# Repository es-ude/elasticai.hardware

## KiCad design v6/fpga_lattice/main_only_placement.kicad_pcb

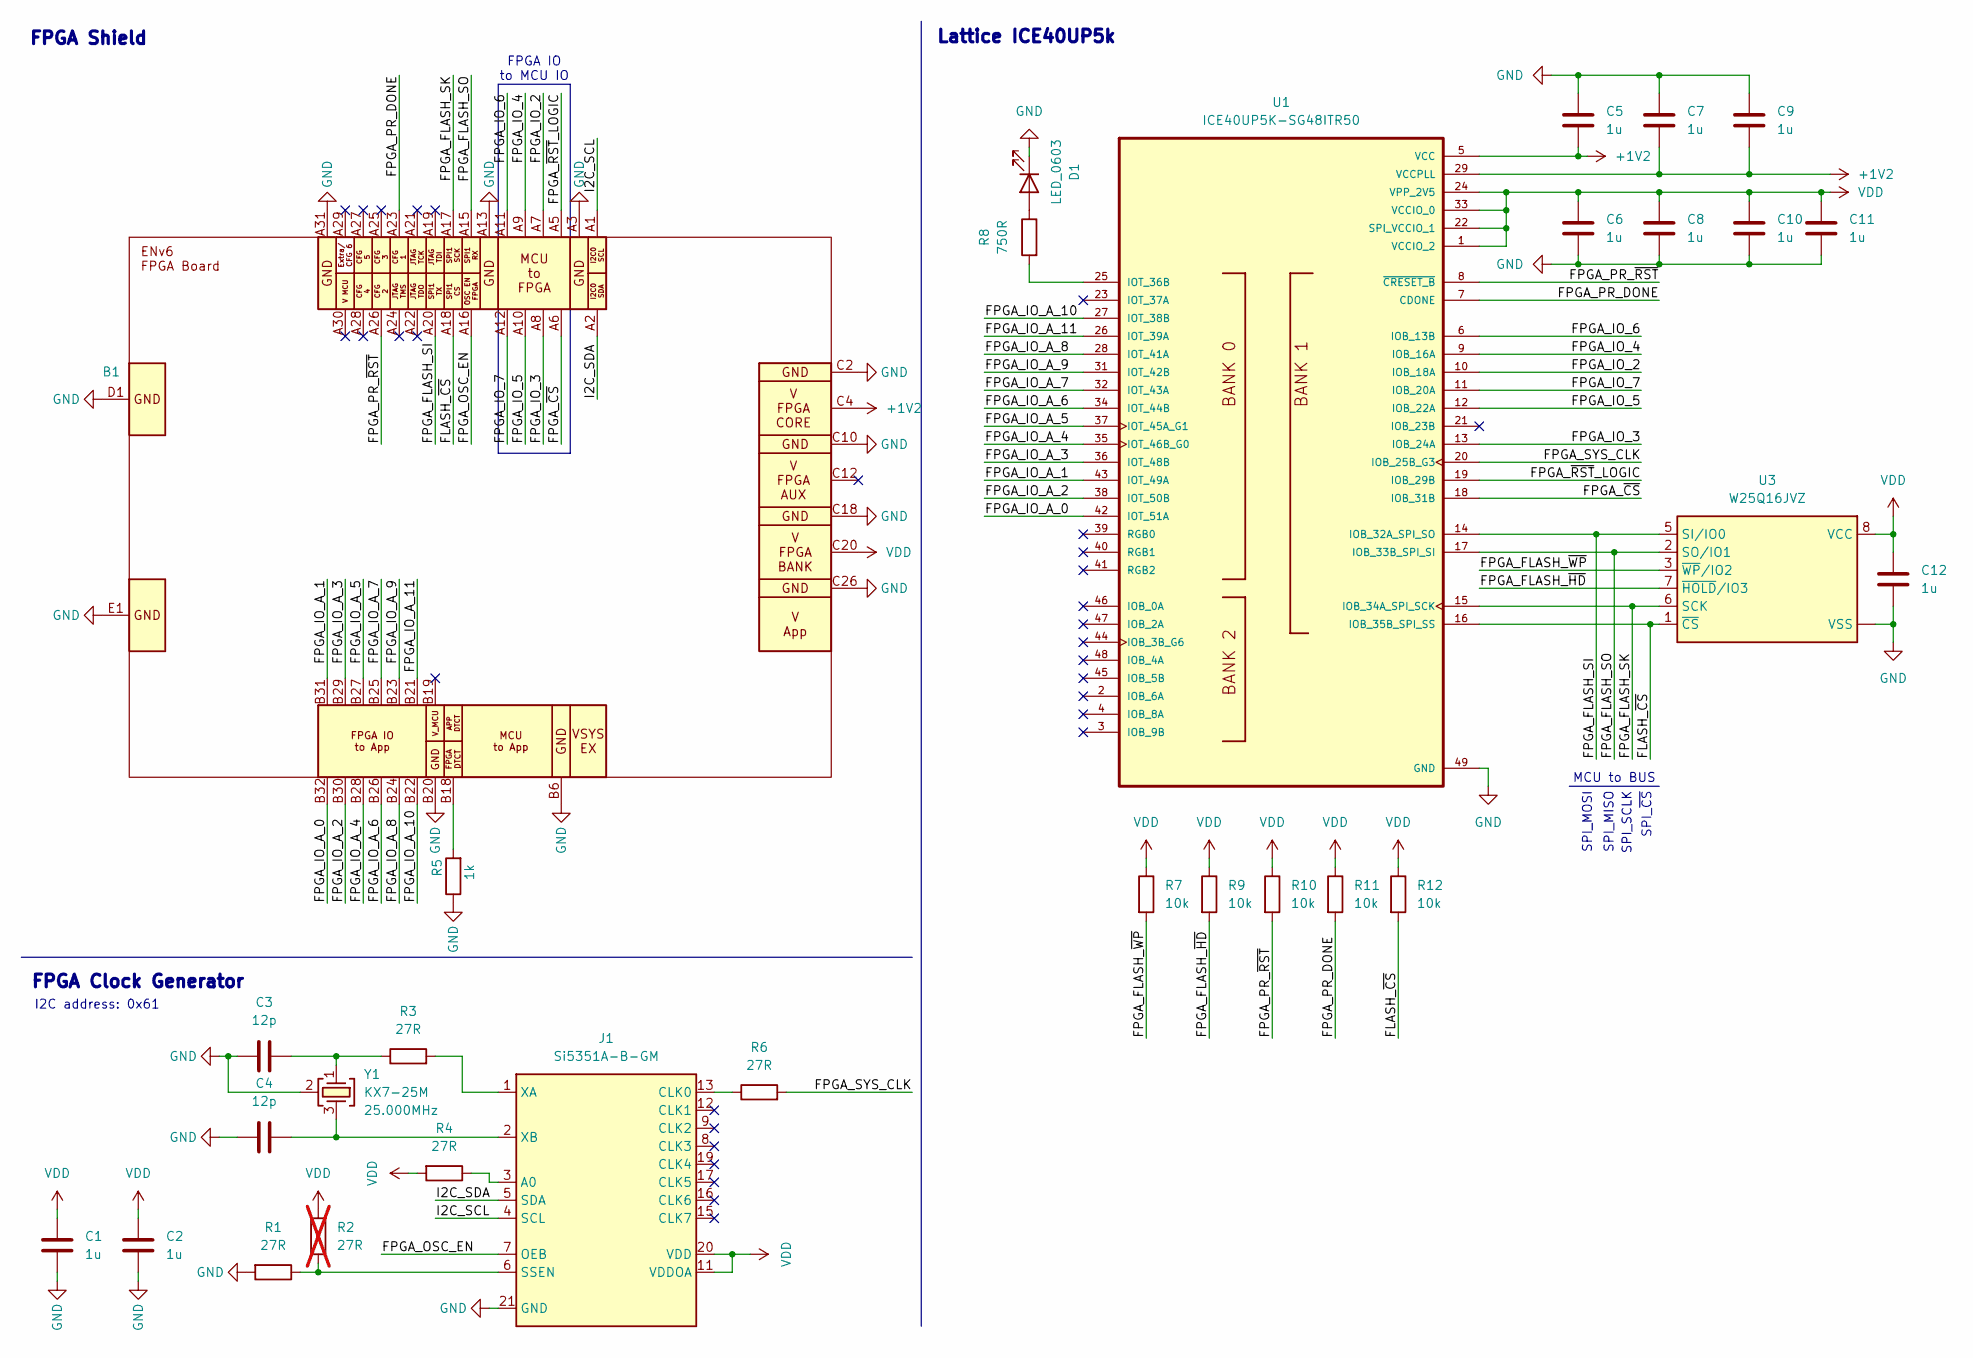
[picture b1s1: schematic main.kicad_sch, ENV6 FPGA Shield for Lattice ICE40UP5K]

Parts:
B1: ExtensionBoard_ENv6
C1, C2, C5, C6, C7, C8, C9, C10, C11, C12: 1u; C_0402_1005Metric
C3, C4: 12p; C_0402_1005Metric
D1: LED_0603; LED_0603_1608Metric
J1: Si5351A-B-GM; QFN-20-1EP_4x4mm_P0.5mm_EP2.7x2.7mm
R1, R3, R4, R6: 27R; R_0402_1005Metric
R2: 27R; R_0402_1005Metric; not fitted
R5: 1k; R_0402_1005Metric
R7, R9, R10, R11, R12: 10k; R_0402_1005Metric
R8: 750R; R_0402_1005Metric
U1: ICE40UP5K-SG48ITR50; QFN-48-1EP_7x7mm_P0.5mm_EP5.15x5.15mm; PARTREV 1.4
U3: W25Q16JVZ; WSON-8-1EP_6x5mm_P1.27mm_EP3.4x4.3mm
Y1: KX7-25M; KX-7; MPN 12.60417

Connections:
+1V2: B1.C3, B1.C4, B1.C5, B1.C6, B1.C7, B1.C8, C5.2, C7.2, C9.2, U1.5 (VCC), U1.29 (VCCPLL), U1.30 (VCC)
/FLASH_~CS: B1.A18, R12.2, U1.16 (IOB_35B_SPI_SS), U3.1 (~CS); also elsewhere on the board
/FPGA_FLASH_SI: B1.A20, U1.14 (IOB_32A_SPI_SO), U3.5 (SI/IO0); also elsewhere on the board
/FPGA_FLASH_SK: B1.A17, U1.15 (IOB_34A_SPI_SCK), U3.6 (SCK); also elsewhere on the board
/FPGA_FLASH_SO: B1.A15, U1.17 (IOB_33B_SPI_SI), U3.2 (SO/IO1); also elsewhere on the board
/FPGA_FLASH_~HD: R9.2, U3.7 (~HOLD/IO3); also elsewhere on the board
/FPGA_FLASH_~WP: R7.2, U3.3 (~WP/IO2); also elsewhere on the board
/FPGA_IO_2: B1.A7, U1.10 (IOB_18A)
/FPGA_IO_3: B1.A8, U1.13 (IOB_24A)
/FPGA_IO_4: B1.A9, U1.9 (IOB_16A)
/FPGA_IO_5: B1.A10, U1.12 (IOB_22A)
/FPGA_IO_6: B1.A11, U1.6 (IOB_13B)
/FPGA_IO_7: B1.A12, U1.11 (IOB_20A)
/FPGA_IO_A_0: B1.B32, U1.42 (IOT_51A)
/FPGA_IO_A_1: B1.B31, U1.43 (IOT_49A)
/FPGA_IO_A_2: B1.B30, U1.38 (IOT_50B)
/FPGA_IO_A_3: B1.B29, U1.36 (IOT_48B)
/FPGA_IO_A_4: B1.B28, U1.35 (IOT_46B_G0)
/FPGA_IO_A_5: B1.B27, U1.37 (IOT_45A_G1)
/FPGA_IO_A_6: B1.B26, U1.34 (IOT_44B)
/FPGA_IO_A_7: B1.B25, U1.32 (IOT_43A)
/FPGA_IO_A_8: B1.B24, U1.28 (IOT_41A)
/FPGA_IO_A_9: B1.B23, U1.31 (IOT_42B)
/FPGA_IO_A_10: B1.B22, U1.27 (IOT_38B)
/FPGA_IO_A_11: B1.B21, U1.26 (IOT_39A)
/FPGA_OSC_EN: B1.A16, J1.7 (OEB)
/FPGA_PR_DONE: B1.A23, R11.2, U1.7 (CDONE)
/FPGA_PR_~RST: B1.A26, R10.2, U1.8 (~CRESET_B)
/FPGA_SYS_CLK: R6.2, U1.20 (IOB_25B_G3)
/FPGA_~CS: B1.A6, U1.18 (IOB_31B)
/FPGA_~RST_LOGIC: B1.A5, U1.19 (IOB_29B)
/I2C_SCL: B1.A1, J1.4 (SCL)
/I2C_SDA: B1.A2, J1.5 (SDA)
GND: B1.A3, B1.A4, B1.A13, B1.A14, B1.A31, B1.A32, B1.B5, B1.B6, B1.B20, B1.C1, B1.C2, B1.C9, B1.C10, B1.C17, B1.C18, B1.C25, B1.C26, B1.D1, B1.D2, B1.D3, B1.D4, B1.D5, B1.D6, B1.D7, B1.D8, B1.E1, B1.E2, B1.E3, B1.E4, B1.E5, B1.E6, B1.E7, B1.E8, C1.2, C2.2, C3.2, C4.2, C5.1, C6.2, C7.1, C8.2, C9.1, C10.2, C11.2, C12.2, D1.1 (K), J1.21 (GND), R1.2, R5.1, U1.49 (GND), U3.4 (VSS), U3.9 (VSS), Y1.2 (SH), Y1.4 (SH); also elsewhere on the board
unnamed: B1.B18, R5.2
unnamed: C3.1, R3.1, Y1.1
unnamed: D1.2 (A), R8.1
unnamed: J1.3 (A0), R4.1
unnamed: J1.13 (CLK0), R6.1
unnamed: J1.6 (SSEN), R1.1, R2.1
unnamed: J1.1 (XA), R3.2
unnamed: C4.1, J1.2 (XB), Y1.3
unnamed: R8.2, U1.25 (IOT_36B)
VDD: B1.C19, B1.C20, B1.C21, B1.C22, B1.C23, B1.C24, C1.1, C2.1, C6.1, C8.1, C10.1, C11.1, C12.1, J1.10 (VDDOB), J1.11 (VDDOA), J1.14 (VDDOD), J1.18 (VDDOC), J1.20 (VDD), R2.2, R4.2, R7.1, R9.1, R10.1, R11.1, R12.1, U1.1 (VCCIO_2), U1.22 (SPI_VCCIO_1), U1.24 (VPP_2V5), U1.33 (VCCIO_0), U3.8 (VCC); also elsewhere on the board

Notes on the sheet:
SPI_MOSI
FPGA IO to MCU IO
SPI_SCLK
MCU to BUS
SPI_MISO
I2C address: 0x61
SPI_~{CS}
FPGA Clock Generator
FPGA Shield
Lattice ICE40UP5k

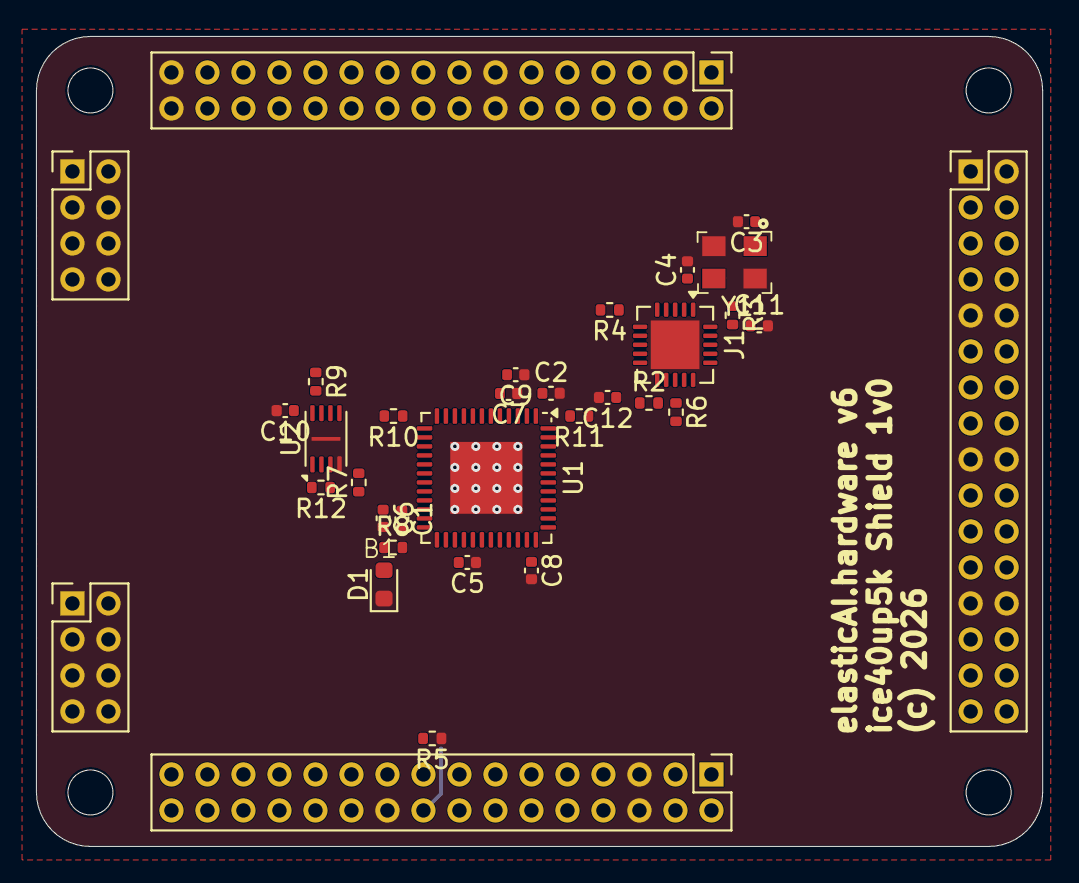
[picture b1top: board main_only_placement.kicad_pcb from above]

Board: 2 copper layers, 55.9 x 45.0 mm, 30 parts (1 on the bottom side), 44 nets.

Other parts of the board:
U2: W25Q16JVUX; USON-8-1EP_3x2mm_P0.5mm_EP0.2x1.6mm

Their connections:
/FLASH_~CS: U2.1 (~CS); also elsewhere on the board
/FPGA_FLASH_SI: U2.5 (SI/IO0); also elsewhere on the board
/FPGA_FLASH_SK: U2.6 (SCK); also elsewhere on the board
/FPGA_FLASH_SO: U2.2 (SO/IO1); also elsewhere on the board
/FPGA_FLASH_~HD: U2.7 (~HOLD/IO3); also elsewhere on the board
/FPGA_FLASH_~WP: U2.3 (~WP/IO2); also elsewhere on the board
GND: U2.4 (VSS), U2.9 (VSS); also elsewhere on the board
VDD: U2.8 (VCC); also elsewhere on the board

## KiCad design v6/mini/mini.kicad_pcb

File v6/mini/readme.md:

# ENv6.mini

Single-board version of the ENv6 platform (revision 1v1): an MCU, an iCE40UP5K FPGA, a power monitor and a PMOD connector on one PCB. It is the smallest entry point / minimal version to the ENv6 idea (MCU-controlled FPGA configuration and per-rail current measurement).
For further details, please look into the [iBOM v1.1](bom/ibom_1v1.html).

## State
Active. Please use the following firmware from this [repo](https://github.com/es-ude/elasticai_runtime_env6mini).

## Concept
ENv6.mini integrates the essentials of the stack on one PCB:
- **MCU:** an RP2350A (U8) with its own QSPI flash (U7), 12 MHz crystal (Y1), USB-C (J1) for power and data, an SWD connector (J3), BOOT/RST buttons (S1, S2) and a WS2812B status LED (D2). The MCU is the master of the board: it configures the FPGA, controls its power and talks to it over SPI.
- **FPGA:** a Lattice iCE40UP5K (U5) with a bitstream flash (U6, W25Q16). The MCU writes the bitstream to this flash over a dedicated flash SPI (SK, SI, SO, CS) and controls the FPGA with `FPGA_RST` (active low); `FPGA_DONE` reports a finished configuration. The control lines `FPGA_CLK`, `FPGA_RST_LOGIC` (active low) and `FPGA_GPIO0 … 5` as well as a second I2C (`I2C_FPGA_SCL/SDA`) connect MCU and FPGA at runtime.
- **User logic:** the FPGA runs the accelerator; data is exchanged with the MCU over the SPI bus (SCLK, MOSI, MISO, CS). Eight FPGA pins (`PMOD_D0 … 7`) are routed to a PMOD connector (U4) at the I/O voltage `VCCQ` for sensors and peripherals.
- **Power and measurement:** two LDOs generate 1.2 V (U2, FPGA core) and 3.3 V (U9, MCU and FPGA I/O). Their outputs pass a PAC1954 power monitor (U1, 1 Ω shunts, I2C, enable `EN_PAC`), so the MCU can measure current and power of the FPGA rails. The FPGA supply can be switched with `PWR_EN_FPGA`. The FPGA I/O bank and the PMOD run at `VCCQ`.

### Differences to the ENv6 stack

|                      | ENv6.mini                  | ENv6 stack                                                |
|----------------------|----------------------------|-----------------------------------------------------------|
| MCU                  | RP2350A                    | RP2354B                                                   |
| FPGA                 | iCE40UP5K, fixed           | exchangeable FPGA board                                   |
| Power                | USB-C, two fixed LDOs      | USB-C / Li-ion, programmable LP873300 with four rails     |
| Current measurement  | PAC1954 on the LDO outputs | PAC1954 on the four programmable rails (or external PPK2) |
| Extension            | PMOD (8 FPGA I/Os)         | MCU/FPGA, application and power headers                   |
| Board identification | –                          | ID resistors, read by the MCU                             |
| Radio / storage      | –                          | Raspberry Pi radio module, microSD                        |

## Contents

| Block (KiCad sheet)                        | Main parts                                                                                                                              |
|--------------------------------------------|-----------------------------------------------------------------------------------------------------------------------------------------|
| MCU (`mcu.kicad_sch`)                      | RP2350A (U8), 12 MHz crystal (Y1), W25Q16 QSPI flash (U7), SWD connector (J3), WS2812B (D2), BOOT / RST buttons (S1, S2), SMA connector |
| FPGA (`fpga.kicad_sch`)                    | Lattice iCE40UP5K-SG48 (U5), W25Q16 bitstream flash (U6), PMOD with 8 GPIOs at VCCQ (U4), status LED, SMA connector                     |
| Connectors / power (`connector.kicad_sch`) | USB-C (J1), PAC1954 (U1, 1 Ω shunts), LDO 1.2 V TLV73312 (U2), LDO 3.3 V TLV73333 (U9)                                                  |

## Interfaces MCU ↔ FPGA

| Interface              | Signals                                                                                |
|------------------------|----------------------------------------------------------------------------------------|
| SPI bus (user logic)   | SCLK, MOSI, MISO, CS                                                                   |
| Flash SPI (bitstream)  | SK, SI, SO, CS                                                                         |
| Control                | `FPGA_CLK`, `FPGA_RST`, `FPGA_RST_LOGIC`, `FPGA_DONE`, `FPGA_GPIO0 … 5`, `PWR_EN_FPGA` |
| I2C to the FPGA        | `I2C_FPGA_SCL`, `I2C_FPGA_SDA`                                                         |
| I2C to the PAC1954     | `I2C_SDA`, `I2C_SCL`, `EN_PAC`                                                         |

Supply rails: VBUS → LDO 1.2 V (FPGA core), LDO 3.3 V (MCU, FPGA I/O), `VCCQ` (FPGA bank, PMOD).

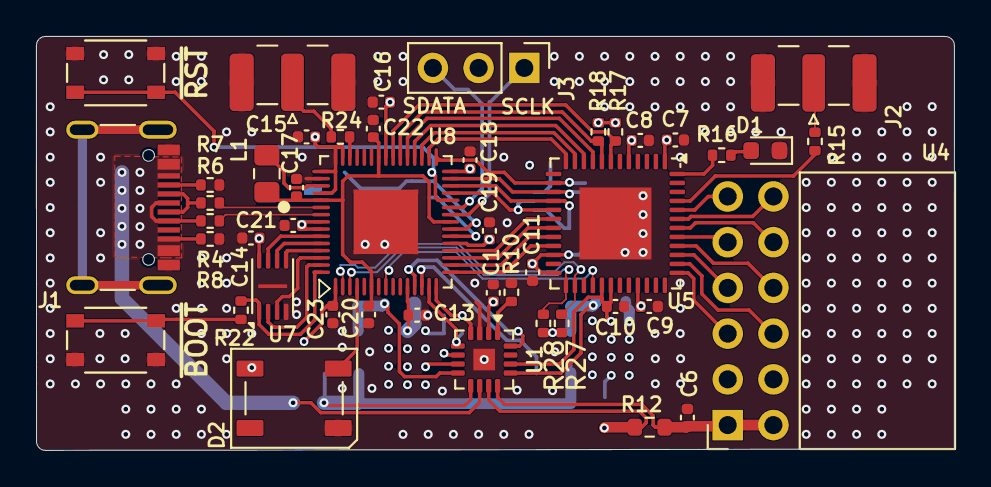
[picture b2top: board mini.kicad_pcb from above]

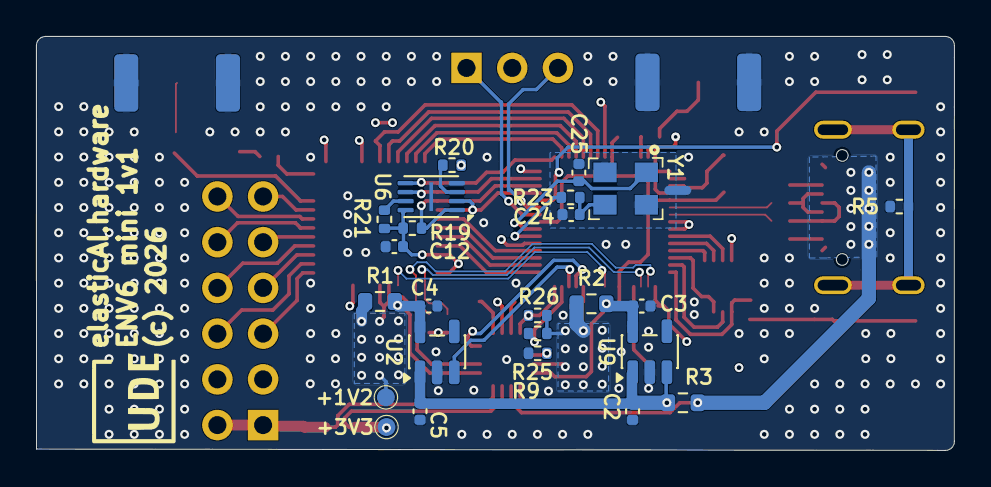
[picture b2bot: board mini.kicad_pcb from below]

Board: 4 copper layers, 51.0 x 23.0 mm, 71 parts (25 on the bottom side), 71 nets.

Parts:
C1, C2, C3, C4, C5, C6, C7, C8, C9, C10, C11, C12, C13, C14, C15, C16, C17, C18, C19, C20, C21, C22, C23: 10u; C_0402_1005Metric
C24, C25: 16p; C_0402_1005Metric
D1: LED_0603; LED_0603_1608Metric
D2: WS2812B; LED_WS2812B_PLCC4_5.0x5.0mm_P3.2mm
J1: USB-C Receptable (16P); USB_C_Receptacle_16P
J2, J4: SMA-FEMALE-H; SMA_Samtec_SMA-J-P-H-ST-EM1_EdgeMount
J3: Pico Debugger (SWD); PinHeader_1x03_P2.54mm_Vertical
L1: 3µ3; L_0805_2012_metric_Alligned_HandSolder
NT1: NetTie_2; NetTie-2_SMD_Pad0.5mm
R1, R2, R3, R12: 1R; R_0603_1608Metric
R4, R6: 27R4; R_0402_1005Metric
R5, R7, R8, R17, R18, R19, R20, R21, R22, R25, R26, R27, R28: 5k1; R_0402_1005Metric
R9, R10, R15, R16, R23, R24: 750R; R_0402_1005Metric
S1: ~{BOOT}; TACTILE-SWITCH
S2: ~{RST}; TACTILE-SWITCH
TP1: +1V2; TestPoint_Pad_D1.0mm
TP2: +3V3; TestPoint_Pad_D1.0mm
U1: PAC1954T-E4Mx; VQFN-16-1EP_3x3mm_P0.5mm_EP1.1x1.1mm
U2: TLV73312PDBV; SOT-23-5
U4: PMOD; PinSocket_2x06_P2.54mm_Horizontal
U5: ICE40UP5K-SG48ITR50; QFN-48-1EP_7x7mm_P0.5mm_EP5.15x5.15mm
U6, U7: W25Q16JVUXIQ; USON-8-1EP_3x2mm_P0.5mm_EP0.2x1.6mm
U8: RP2350A; QFN-60_EP_7x7_Pitch0.4mm
U9: TLV73333PDBV; SOT-23-5
Y1: KX7_12M; KX-7

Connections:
+1V1: C17.2, C20.2, C22.2, L1.1, U8.6 (DVDD_1V1), U8.23 (DVDD_1V1), U8.39 (DVDD_1V1), U8.50 (VREG_FB)
+1V2: C8.2, C10.2, R1.1, TP1.1 (1_1), U1.14 (SENSE2-), U5.5 (VCC), U5.29 (VCCPLL), U5.30 (VCC)
/Connectors/USB_PWRIN: J1.A4 (VBUS), J1.A9 (VBUS), J1.B4 (VBUS), J1.B9 (VBUS), R3.2, U1.10 (SENSE4+)
/Connectors/VLDO_1V2: C4.2, R1.2, U1.13 (SENSE2+), U2.5 (OUT)
/Connectors/VLDO_3V3: C3.2, R2.2, U1.8 (SENSE3+), U9.5 (OUT)
/FPGA/FPGA_FLASH_~HD: R21.2, U6.7 (~HOLD/IO3)
/FPGA/FPGA_FLASH_~WP: R20.2, U6.3 (~WP/IO2)
/FPGA/PMOD_D0: U4.5 (D0), U5.37 (IOT_45A_G1)
/FPGA/PMOD_D1: U4.6 (D1), U5.38 (IOT_50B)
/FPGA/PMOD_D2: U4.7 (D2), U5.39 (RGB0)
/FPGA/PMOD_D3: U4.8 (D3), U5.40 (RGB1)
/FPGA/PMOD_D4: U4.9 (D4), U5.41 (RGB2)
/FPGA/PMOD_D5: U4.10 (D5), U5.42 (IOT_51A)
/FPGA/PMOD_D6: U4.11 (D6), U5.44 (IOB_3B_G6)
/FPGA/PMOD_D7: U4.12 (D7), U5.43 (IOT_49A)
/MCU/GND_QRZ: C24.1, C25.1, NT1.2, Y1.2 (SH), Y1.4 (SH)
EN_PAC: U1.16 (~PWRDN), U8.12 (GPIO_08)
FPGA_CLK: U5.9 (IOB_16A), U8.35 (GPIO_23)
FPGA_DONE: R17.2, U5.7 (CDONE), U8.37 (GPIO_25)
FPGA_FLASH_SI: U5.14 (IOB_32A_SPI_SO), U6.5 (SI/IO0), U8.31 (GPIO_19)
FPGA_FLASH_SK: U5.15 (IOB_34A_SPI_SCK), U6.6 (SCK), U8.29 (GPIO_18)
FPGA_FLASH_SO: U5.17 (IOB_33B_SPI_SI), U6.2 (SO/IO1), U8.27 (GPIO_16)
FPGA_FLASH_~CS: R19.2, U5.16 (IOB_35B_SPI_SS), U6.1 (~CS), U8.28 (GPIO_17)
FPGA_GPIO0: U5.12 (IOB_22A), U8.32 (GPIO_20)
FPGA_GPIO1: U5.11 (IOB_20A), U8.33 (GPIO_21)
FPGA_GPIO2: U5.21 (IOB_23B), U8.16 (GPIO_12)
FPGA_GPIO3: U5.19 (IOB_29B), U8.18 (GPIO_14)
FPGA_GPIO4: U5.18 (IOB_31B), U8.19 (GPIO_15)
FPGA_GPIO5: U5.28 (IOT_41A), U8.8 (GPIO_05)
FPGA_~CS: U5.20 (IOB_25B_G3), U8.17 (GPIO_13)
FPGA_~RST: R18.2, U5.8 (~CRESET_B), U8.36 (GPIO_24)
FPGA_~RST_LOGIC: U5.10 (IOB_18A), U8.34 (GPIO_22)
GNDD: C1.1, C2.1, C3.1, C4.1, C5.1, C6.2, C7.2, C8.1, C9.2, C10.1, C11.2, C12.2, C13.1, C14.2, C15.1, C16.1, C17.1, C18.1, C19.1, C20.1, C21.1, C22.1, C23.1, D1.1 (K), D2.3 (VSS), J1.A1 (GND), J1.A12 (GND), J1.B1 (GND), J1.B12 (GND), J2.2 (GND), J3.2 (GND), J4.2 (GND), NT1.1, R5.2, R7.1, R8.1, R9.2, R10.2, S1.1, S1.2 (1), S2.1, S2.2 (1), U1.3 (GND), U1.17 (EP), U2.2 (GND), U4.3 (GND), U4.4 (GND), U5.49 (GND), U6.4 (VSS), U6.9 (VSS), U7.4 (VSS), U7.9 (VSS), U8.47 (GND), U8.61 (GND), U9.2 (GND)
I2C_FPGA_SCL: R28.2, U5.25 (IOT_36B), U8.3 (GPIO_01)
I2C_FPGA_SDA: R27.2, U5.26 (IOT_39A), U8.2 (GPIO_00)
I2C_SCL: R26.2, U1.4 (SCL), U8.15 (GPIO_11)
I2C_SDA: R25.2, U1.5 (SDA), U8.14 (GPIO_10)
unnamed: C24.2, R23.1, Y1.3
unnamed: D1.2 (A), R16.1
unnamed: D2.4 (DIN), U8.4 (GPIO_02)
unnamed: J1.A5 (CC1), R7.2
unnamed: J1.B5 (CC2), R8.2
unnamed: J1.A6 (D+), J1.B6 (D+), R4.1
unnamed: J1.A7 (D-), J1.B7 (D-), R6.1
unnamed: J1.S1 (SHIELD), R5.1
unnamed: J2.1 (SIG), R15.2
unnamed: J3.1 (SCLK), U8.24 (SWCLK)
unnamed: J3.3 (SDATA), U8.25 (SWDIO)
unnamed: J4.1 (SIG), R24.2
unnamed: R22.2, S1.3 (2), S1.4 (2)
unnamed: R9.1, U1.6 (ADDRSEL)
unnamed: R10.1, U1.1 (SLOW)
unnamed: R16.2, U5.48 (IOB_4A)
unnamed: R15.1, U5.45 (IOB_5B)
unnamed: U7.6 (SCK), U8.56 (QSPI_CLK)
unnamed: U7.5 (SI/IO0), U8.57 (QSPI_SD0)
unnamed: U7.2 (SO/IO1), U8.59 (QSPI_SD1)
unnamed: R22.1, U7.1 (~CS), U8.60 (QSPI_SS)
unnamed: U7.7 (~HOLD/IO3), U8.55 (QSPI_SD3)
unnamed: U7.3 (~WP/IO2), U8.58 (QSPI_SD2)
unnamed: R24.1, U8.43 (GPIO_29_ADC3)
unnamed: S2.3 (2), S2.4 (2), U8.26 (RUN)
unnamed: L1.2, U8.48 (VREG_LX)
unnamed: R23.2, U8.21 (XIN)
unnamed: C25.2, U8.22 (XOUT), Y1.1
PWR_EN_FPGA: U2.3 (EN), U8.13 (GPIO_09)
USB_DN: R6.2, U8.51 (USB_DM)
USB_DP: R4.2, U8.52 (USB_DP)
VCCQ: C6.1, R12.1, U1.12 (SENSE1-), U4.1 (VCC), U4.2 (VCC)
VDD: C1.2, C7.1, C9.1, C11.1, C12.1, C13.2, C14.1, C15.2, C16.2, C18.2, C19.2, C21.2, C23.2, D2.1 (VDD), R2.1, R12.2, R17.1, R18.1, R19.1, R20.1, R21.1, R25.1, R26.1, R27.1, R28.1, TP2.1 (1_1), U1.2 (V_{DD}), U1.7 (SENSE3-), U1.11 (SENSE1+), U5.1 (VCCIO_2), U5.22 (SPI_VCCIO_1), U5.24 (VPP_2V5), U5.33 (VCCIO_0), U6.8 (VCC), U7.8 (VCC), U8.1 (IOVDD), U8.11 (IOVDD), U8.20 (IOVDD), U8.30 (IOVDD), U8.38 (IOVDD), U8.44 (AVDD_ADC), U8.45 (IOVDD), U8.46 (VREG_AVDD), U8.49 (VREG_IN), U8.53 (USB_OTP_VDD), U8.54 (IOVDD_QSPI)
VPWR_USB: C2.2, C5.2, R3.1, U1.9 (SENSE4-), U2.1 (IN), U9.1 (IN), U9.3 (EN)

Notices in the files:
v6/fpga_lattice/main_only_placement.kicad_pcb:
(c) 2026
parts and their libraries:
License: Apache-2.0
